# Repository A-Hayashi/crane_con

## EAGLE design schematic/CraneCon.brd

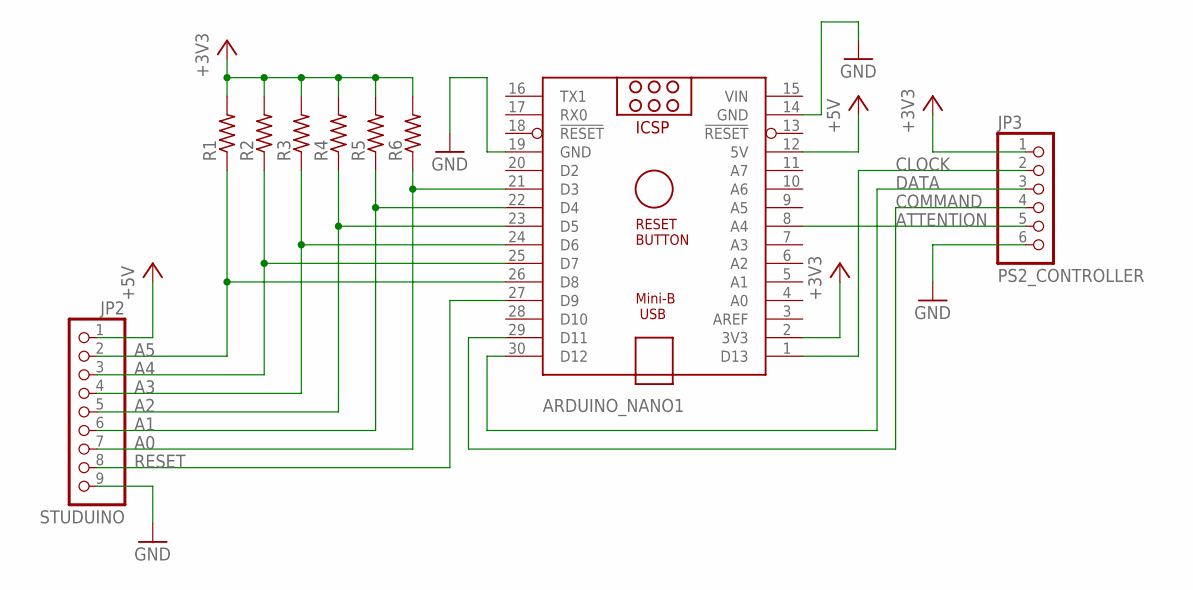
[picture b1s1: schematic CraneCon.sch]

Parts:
ARDUINO_NANO1: ARDUINO_NANO
JP2: STUDUINO; 1X09
JP3: PS2_CONTROLLER; 1X06
R1, R2, R3, R4, R5, R6: R-US_0204/7; 0204/7

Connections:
+3V3: ARDUINO_NANO1.2 (3V3), JP3.1, R1.2, R2.2, R3.2, R4.2, R5.2, R6.2
+5V: ARDUINO_NANO1.12 (5V), JP2.1
A0: ARDUINO_NANO1.21 (D3), JP2.7, R6.1
A1: ARDUINO_NANO1.22 (D4), JP2.6, R5.1
A2: ARDUINO_NANO1.23 (D5), JP2.5, R4.1
A3: ARDUINO_NANO1.24 (D6), JP2.4, R3.1
A4: ARDUINO_NANO1.25 (D7), JP2.3, R2.1
A5: ARDUINO_NANO1.26 (D8), JP2.2, R1.1
ATTENTION: ARDUINO_NANO1.8 (A4), JP3.5
CLOCK: ARDUINO_NANO1.1 (D13), JP3.2
COMMAND: ARDUINO_NANO1.29 (D11), JP3.4
DATA: ARDUINO_NANO1.30 (D12), JP3.3
GND: ARDUINO_NANO1.14 (GND), ARDUINO_NANO1.19 (GND), JP2.9, JP3.6
RESET: ARDUINO_NANO1.27 (D9), JP2.8
VIN: ARDUINO_NANO1.15 (VIN)

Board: 2 copper layers, 9 parts (0 on the bottom side), 14 nets, no tracks yet.

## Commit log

2019-01-10 PS2コントローラ動作OK
2019-01-11 回路図追加
